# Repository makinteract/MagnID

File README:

1) As stated in the license, the software is provided as is, without warranty of any kind.

2) At the moment, we do not offer any suport with the software. If you have problems with the installation or operating the software, we might not be able to help you or support you. The software comes as is. We however encourage you to check out this repository in future, as we are planning to add a tutorial session (or a video tutorial) - but it is only a plan for the moment.

3) We applied to a patent about the MagnID in the Republic of Korea in 2014. The patent is still pending.

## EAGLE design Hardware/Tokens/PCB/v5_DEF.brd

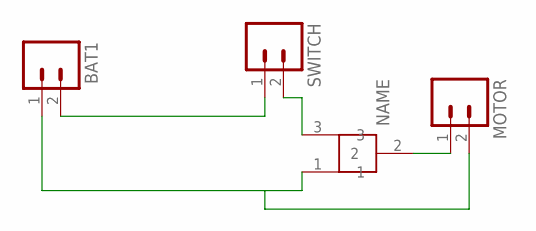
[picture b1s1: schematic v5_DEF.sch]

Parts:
BAT1: M02-JST-2-PTH-NO_SILK; JST-2-PTH-NS
MOTOR: M02-JST-2-PTH-NO_SILK; JST-2-PTH-NS
SWITCH: M02-JST-2-PTH-NO_SILK; JST-2-PTH-NS
U$1: BOURNS3313JBOURNS3313J; BOURNS3313J

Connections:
GND: BAT1.1, MOTOR.2, U$1.1
unnamed: BAT1.2, SWITCH.1
unnamed: SWITCH.2, U$1.3
unnamed: MOTOR.1, U$1.2

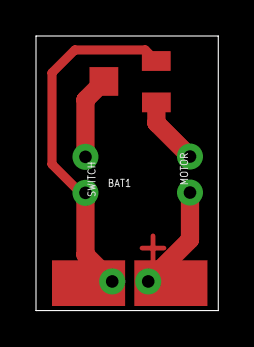
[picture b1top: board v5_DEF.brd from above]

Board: 2 copper layers, 10.1 x 15.3 mm, 4 parts (0 on the bottom side), 4 nets.

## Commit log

2015-01-12 Software and hardware file - initial upload
2015-01-12 added README

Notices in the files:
parts and their libraries:
SparkFun-Connectors: Licensing: CC v3.0 Share-Alike You are welcome to use this library for commercial purposes.
